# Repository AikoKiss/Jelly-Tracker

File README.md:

# Puchi Tracker
A smol-slime style tracker, with only the top-end parts, double-sided, NRF54L10 with ICM45686+QMC6309. Battery life is to be tested.

Thank you to Crylog for being an Absolute chad and unit of a PCB designer.
+ Mumo Tracker for the nice footprints and 3D files, making it easier to design the PCB.
+ Thank you, the slime community, for bullying all the bugs out of my design.
+ Special thanks to Meia for taking the time to help me squash all my stupid decisions and bugs.

## License

This project is source-available for personal and
educational use only.

Commercial use, manufacturing, resale, or distribution
For-profit is prohibited without written permission
from Limeneer Labs.

See the [LICENSE](LICENSE) file for full details.

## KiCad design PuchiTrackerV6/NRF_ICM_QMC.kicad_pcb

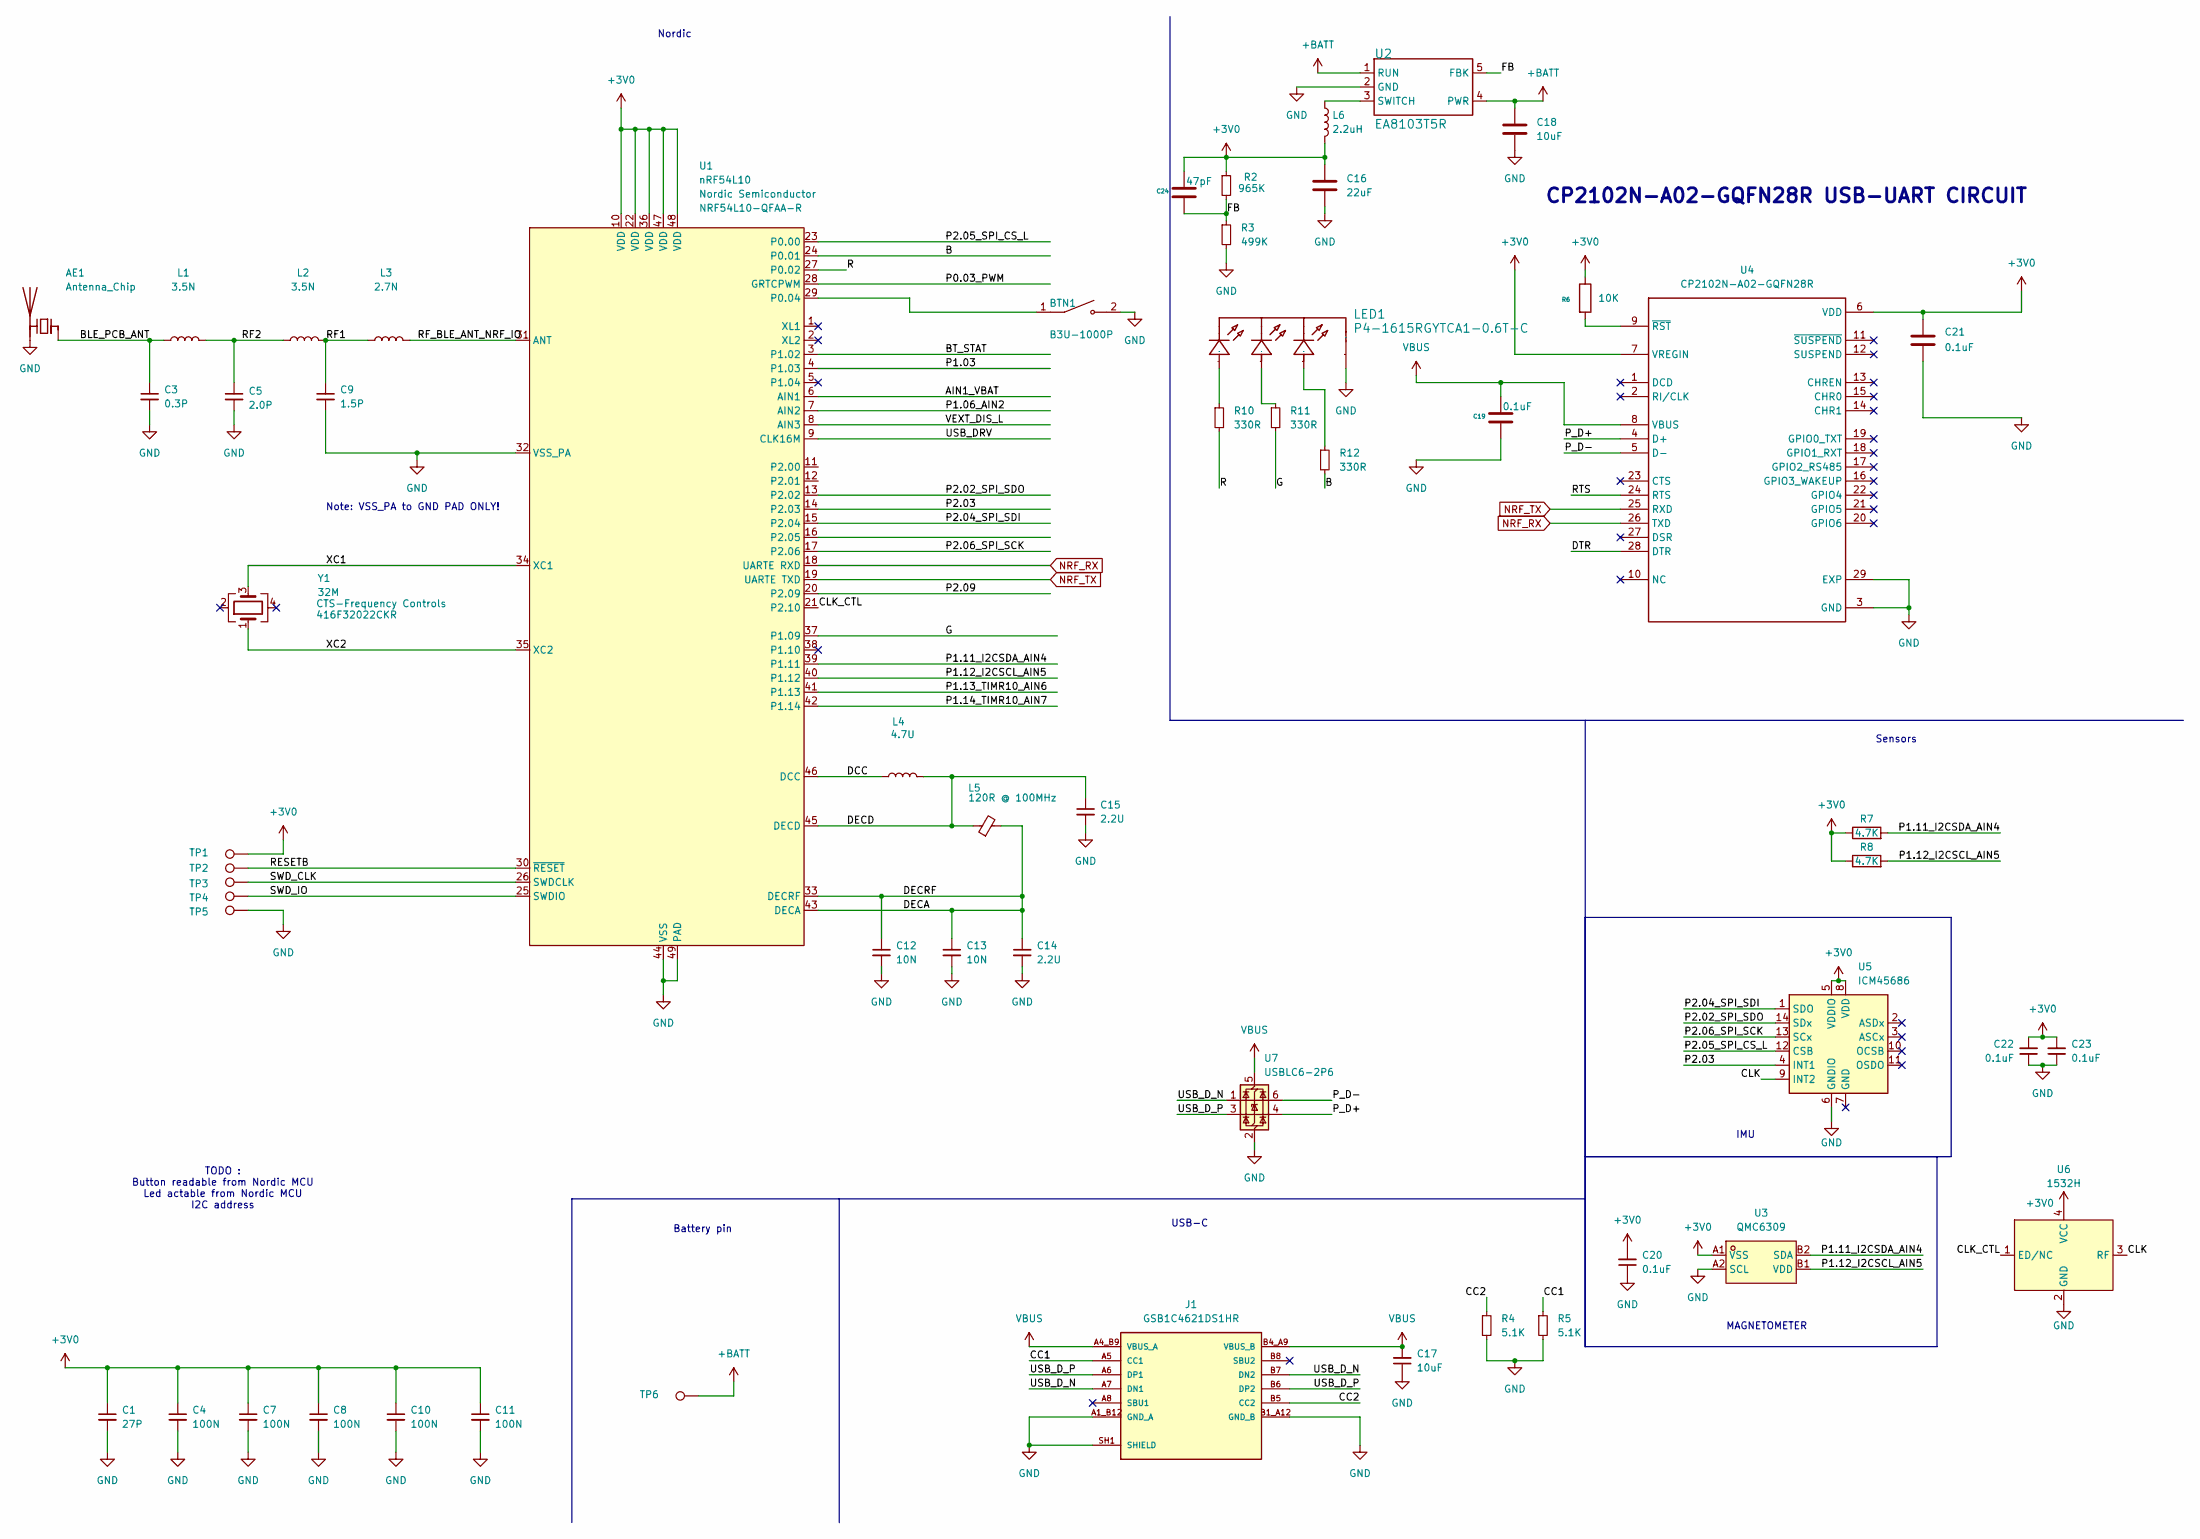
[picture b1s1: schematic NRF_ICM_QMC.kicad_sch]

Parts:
AE1: Antenna_Chip; MFG_PN 2450AT18A0100001E
BTN1: B3U-1000P; SW_SPST_B3U-1000P
C1: 27P; C_0402_1005Metric
C3: 0.3P; C_0402_1005Metric; MFG_PN GJM1555C1HR30WB01D
C4, C7, C8, C10, C11: 100N; C_0402_1005Metric
C5: 2.0P; C_0402_1005Metric; MFG_PN GJM0335C1E2R0WB01
C9: 1.5P; C_0402_1005Metric; MFG_PN GJM0335C1E1R5WB01
C12, C13: 10N; C_0402_1005Metric
C14, C15: 2.2U; C_0402_1005Metric
C16: 22uF; C_0402_1005Metric
C17, C18: 10uF; C_0402_1005Metric
C19, C20, C21, C22, C23: 0.1uF; C_0402_1005Metric
C24: 47pF; C_0402_1005Metric
J1: GSB1C4621DS1HR; AMPHENOL_GSB1C4621DS1HR; PARTREV AX1
L1, L2: 3.5N; L_0201_0603Metric; MFG_PN LQP03HQ3N5B02
L3: 2.7N; L_0201_0603Metric; MFG_PN LQP03HQ2N7B02
L4: 4.7U; L_0402_1005Metric; MFG_PN PLEA67BCA4R7M-1PT00
L5: 120R @ 100MHz; L_0201_0603Metric; MFG_PN BLM03AG121SN1D
L6: 2.2uH; L_1210_3225Metric
LED1: P4-1615RGYTCA1-0.6T-C; RGB; Manufacturer Part P4-1615RGYTCA1-0.6T-C; LCSC Part Name RGY三色
R2: 965K; R_0201_0603Metric
R3: 499K; R_0201_0603Metric
R4, R5: 5.1K; R_0201_0603Metric
R6: 10K; C_0402_1005Metric
R7, R8: 4.7K; R_0402_1005Metric
R10, R11, R12: 330R; R_0201_0603Metric
TP1, TP2, TP3, TP4, TP5, TP6: TestPoint; TestPoint_Pad_D1.0mm
U1: nRF54L10; QFN-48-1EP_6x6mm_P0.4mm_EP4.6x4.6mm; MFG_PN NRF54L10-QFAA-R
U2: EA8103T5R; Manufacturer Part EA8103T5R; LCSC Part Name 降压型 1.2A 2.6V~6V
U3: QMC6309; X1-WLB0808-4_L0.8-W0.8-P0.40-TL; MPN QMC6309; LCSC Part C5439871
U4: CP2102N-A02-GQFN28R; QFN-28-1EP_5x5mm_P0.5mm_EP3.1x3.1mm; PARTREV 1.5
U5: ICM45686; IMU (1)
U6: 1532H; CLK
U7: USBLC6-2P6; SOT-666
Y1: 32M; Oscillator_SMD_Abracon_ASCO-4Pin_1.6x1.2mm; MFG_PN 416F32022CKR

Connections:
+3V0: C1.1, C4.1, C7.1, C8.1, C10.1, C11.1, C16.1, C20.2, C21.1, C22.2, C23.2, C24.1, L6.2, R2.1, R6.1, R7.1, R8.1, TP1.1 (1_1), U1.10 (VDD), U1.22 (VDD), U1.36 (VDD), U1.47 (VDD), U1.48 (VDD), U3.A1 (VSS), U4.6 (VDD), U4.7 (VREGIN), U5.5 (VDDIO), U5.8 (VDD), U6.4 (VCC)
+BATT: C18.1, TP6.1 (1_1), U2.1 (RUN), U2.4 (PWR)
/AIN1_VBAT: U1.6 (AIN1)
/B: R12.2, U1.24 (P0.01)
/BLE_PCB_ANT: AE1.1 (FEED), C3.1, L1.1
/BT_STAT: U1.3 (P1.02)
/CC1: J1.A5 (CC1), R5.1
/CC2: J1.B5 (CC2), R4.1
/CLK: U5.9 (INT2), U6.3 (RF)
/CLK_CTL: U1.21 (P2.10), U6.1 (ED/NC)
/DCC: L4.1, U1.46 (DCC)
/DECA: C12.1, C13.1, C14.1, L5.2, U1.33 (DECRF), U1.43 (DECA)
/DECD: C15.1, L4.2, L5.1, U1.45 (DECD)
/DTR: U4.28 (DTR)
/FB: C24.2, R2.2, R3.1, U2.5 (FBK)
/G: R11.2, U1.37 (P1.09)
/P0.03_PWM: U1.28 (GRTCPWM)
/P1.03: U1.4 (P1.03)
/P1.06_AIN2: U1.7 (AIN2)
/P1.11_I2CSDA_AIN4: R7.2, U1.39 (P1.11), U3.B2 (SDA)
/P1.12_I2CSCL_AIN5: R8.2, U1.40 (P1.12), U3.B1 (VDD)
/P1.13_TIMR10_AIN6: U1.41 (P1.13)
/P1.14_TIMR10_AIN7: U1.42 (P1.14)
/P2.02_SPI_SDO: U1.13 (P2.02), U5.14 (SDx)
/P2.03: U1.14 (P2.03), U5.4 (INT1)
/P2.04_SPI_SDI: U1.15 (P2.04), U5.1 (SDO)
/P2.05_SPI_CS_L: U1.23 (P0.00), U5.12 (CSB)
/P2.06_SPI_SCK: U1.17 (P2.06), U5.13 (SCx)
/P2.09: U1.20 (P2.09)
/P_D+: U4.4 (D+), U7.4 (I/O2)
/P_D-: U4.5 (D-), U7.6 (I/O1)
/R: R10.2, U1.27 (P0.02)
/RESETB: TP2.1 (1_1), U1.30 (~RESET)
/RF1: C9.1, L2.2, L3.1
/RF2: C5.1, L1.2, L2.1
/RF_BLE_ANT_NRF_IO: L3.2, U1.31 (ANT)
/RTS: U4.24 (RTS)
/SWD_CLK: TP3.1 (1_1), U1.26 (SWDCLK)
/SWD_IO: TP4.1 (1_1), U1.25 (SWDIO)
/USB_DRV: U1.9 (CLK16M)
/USB_D_N: J1.A7 (DN1), J1.B7 (DN2), U7.1 (I/O1)
/USB_D_P: J1.A6 (DP1), J1.B6 (DP2), U7.3 (I/O2)
/VEXT_DIS_L: U1.8 (AIN3)
/XC1: U1.34 (XC1), Y1.3
/XC2: U1.35 (XC2), Y1.1
GND: AE1.2 (PCB_Trace), BTN1.2, C1.2, C3.2, C4.2, C5.2, C7.2, C8.2, C9.2, C10.2, C11.2, C12.2, C13.2, C14.2, C15.2, C16.2, C17.1, C18.2, C19.2, C20.1, C21.2, C22.1, C23.1, J1.A1_B12 (GND_A), J1.B1_A12 (GND_B), J1.SH1 (SHIELD), J1.SH2 (SHIELD), J1.SH3 (SHIELD), J1.SH4 (SHIELD), LED1.1 (V), R3.2, R4.2, R5.2, TP5.1 (1_1), U1.32 (VSS_PA), U1.44 (VSS), U1.49 (PAD), U2.2 (GND), U3.A2 (SCL), U4.3 (GND), U4.29 (EXP), U5.6 (GNDIO), U6.2 (GND), U7.2 (GND)
NRF_RX: U1.18 (UARTE RXD), U4.26 (TXD)
NRF_TX: U1.19 (UARTE TXD), U4.25 (RXD)
unnamed: LED1.4 (B), R12.1
unnamed: LED1.3 (G), R11.1
unnamed: LED1.2 (R), R10.1
unnamed: BTN1.1, U1.29 (P0.04)
unnamed: L6.1, U2.3 (SWITCH)
unnamed: R6.2, U4.9 (~RST)
VBUS: C17.2, C19.1, J1.A4_B9 (VBUS_A), J1.B4_A9 (VBUS_B), U4.8 (VBUS), U7.5 (VBUS)

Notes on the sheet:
Nordic
USB-C
MAGNETOMETER
TODO : Button readable from Nordic MCU Led actable from Nordic MCU I2C address
Note: VSS_PA to GND PAD ONLY!
IMU
Sensors
Battery pin
CP2102N-A02-GQFN28R USB-UART CIRCUIT

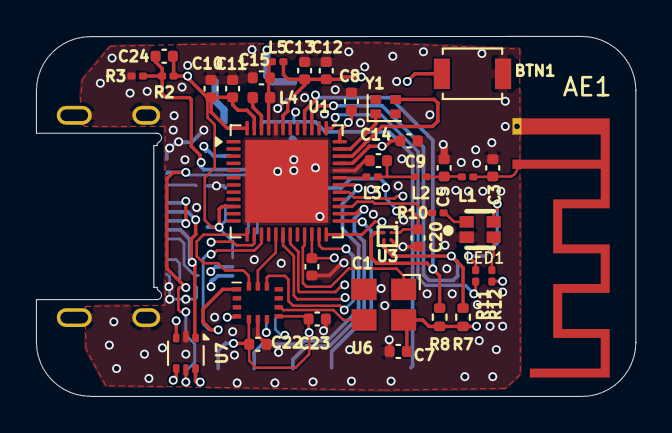
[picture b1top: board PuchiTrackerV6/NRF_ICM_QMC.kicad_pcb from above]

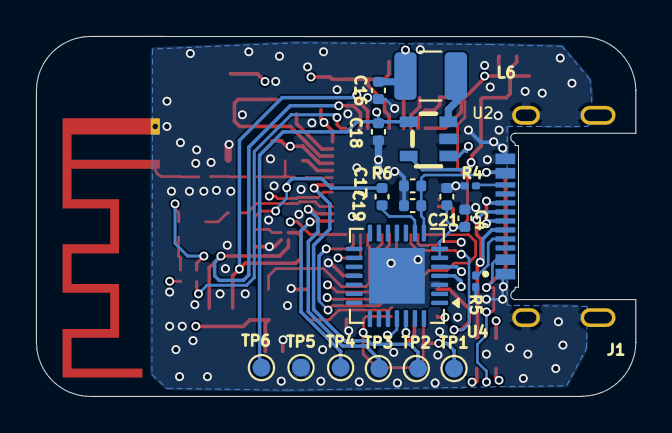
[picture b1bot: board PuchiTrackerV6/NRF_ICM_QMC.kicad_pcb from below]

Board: 4 copper layers, 33.3 x 20.0 mm, 56 parts (19 on the bottom side), 43 nets.

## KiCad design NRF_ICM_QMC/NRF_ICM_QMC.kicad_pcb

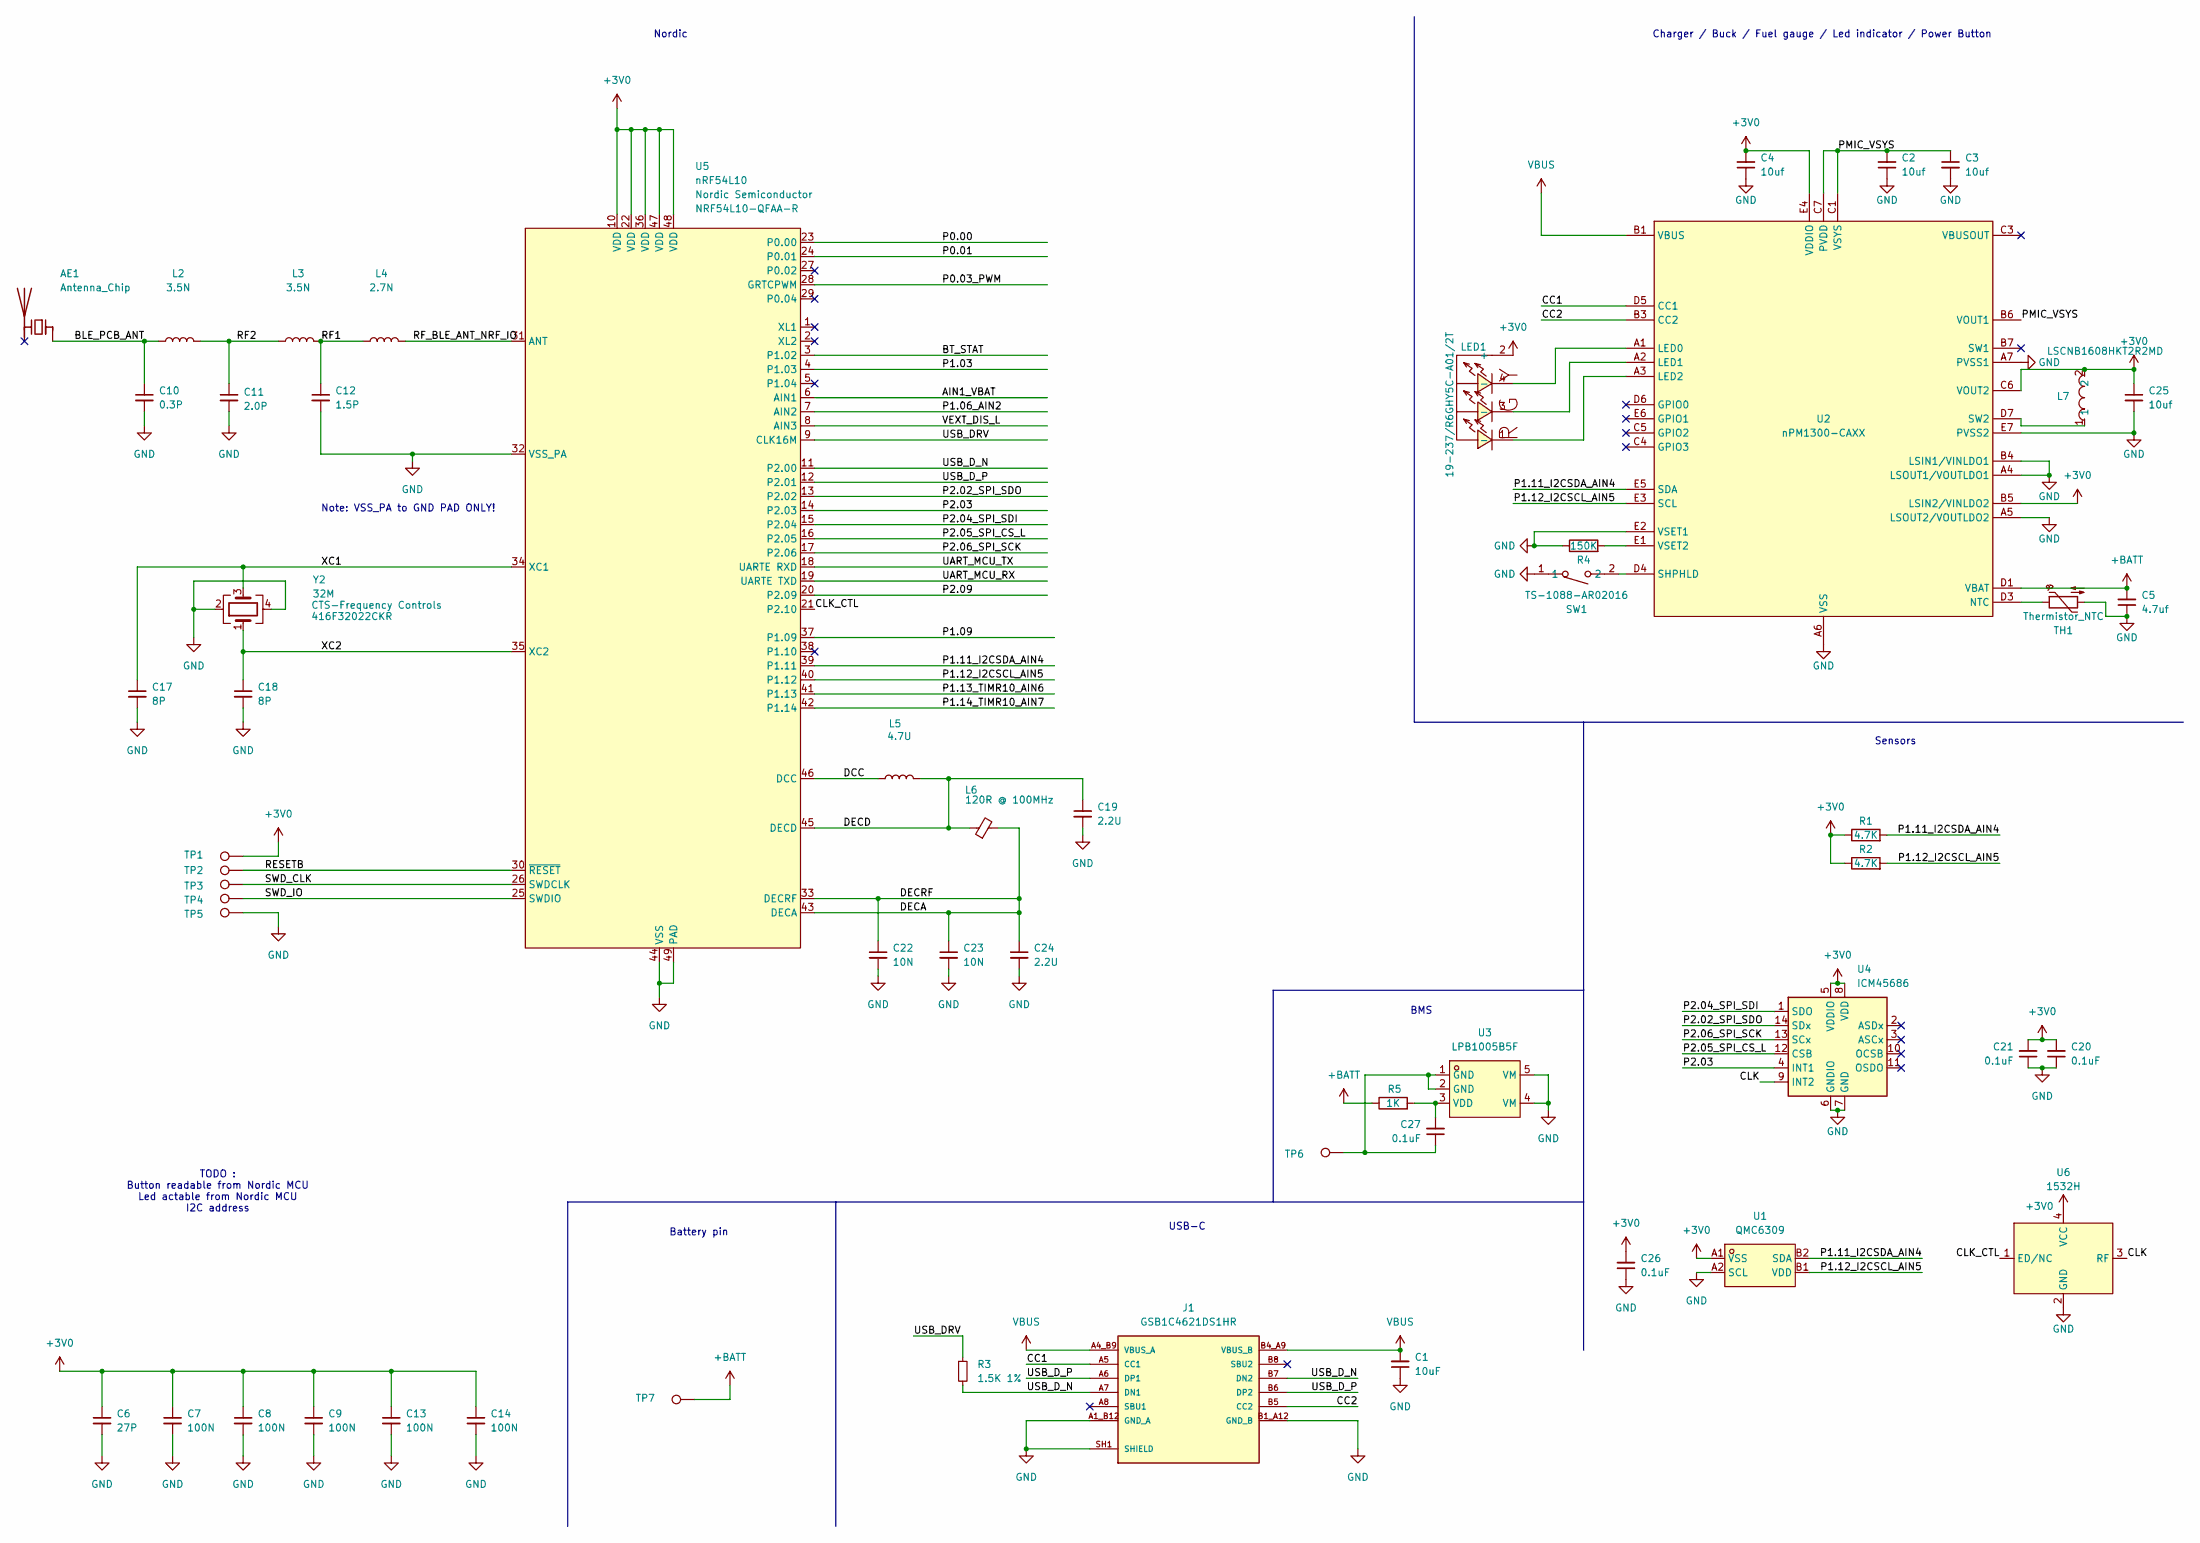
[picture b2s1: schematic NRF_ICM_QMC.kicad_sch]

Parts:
AE1: Antenna_Chip; Johanson_2450AT18x100; MFG_PN 2450AT18A0100001E
C1: 10uF; C_0805_2012Metric
C2, C3, C4, C25: 10uf; C_0805_2012Metric
C5: 4.7uf; C_0402_1005Metric
C6: 27P; C_0402_1005Metric
C7, C8, C9, C13, C14: 100N; C_0402_1005Metric
C10: 0.3P; C_0402_1005Metric; MFG_PN GJM1555C1HR30WB01D
C11: 2.0P; C_0402_1005Metric; MFG_PN GJM0335C1E2R0WB01
C12: 1.5P; C_0402_1005Metric; MFG_PN GJM0335C1E1R5WB01
C17, C18: 8P; C_0402_1005Metric
C19, C24: 2.2U; C_0402_1005Metric
C20, C21, C27: 0.1uF; C_0402_1005Metric
C22, C23: 10N; C_0402_1005Metric
C26: 0.1uF; C_0805_2012Metric
J1: GSB1C4621DS1HR; AMPHENOL_GSB1C4621DS1HR; PARTREV AX1
L2, L3: 3.5N; L_0201_0603Metric; MFG_PN LQP03HQ3N5B02
L4: 2.7N; L_0201_0603Metric; MFG_PN LQP03HQ2N7B02
L5: 4.7U; L_0402_1005Metric; MFG_PN PLEA67BCA4R7M-1PT00
L6: 120R @ 100MHz; L_0201_0603Metric; MFG_PN BLM03AG121SN1D
L7: LSCNB1608HKT2R2MD; L0603; MPN LSCNB1608HKT2R2MD; LCSC Part C6079477
LED1: 19-237/R6GHY5C-A01/2T; LED-ARRAY-SMD_4P-L1.6-W1.6-BL-CW; MPN 19-237/R6GHY5C-A01/2T; LCSC Part C2897364
R1, R2: 4.7K; R_0402_1005Metric
R3: 1.5K 1%; R_0201_0603Metric
R4: 150K; R_0402_1005Metric
R5: 1K
SW1: TS-1088-AR02016; SW-SMD_L3.9-W3.0-P4.45; MPN TS-1088-AR02016; LCSC Part C720477
TH1: Thermistor_NTC
TP1, TP2, TP3, TP4, TP5, TP6, TP7: TestPoint; TestPoint_Pad_D1.0mm
U1: QMC6309; X1-WLB0808-4_L0.8-W0.8-P0.40-TL; MPN QMC6309; LCSC Part C5439871
U2: nPM1300-CAXX; BGA-35_7x5_3.077x2.3775mm
U3: LPB1005B5F; SOT-23-5_L2.9-W1.6-P0.95-LS2.9-BL; MPN LPB1005B5F; LCSC Part C42460087
U4: ICM45686; Bosch_LGA-14_3x2.5mm_P0.5mm
U5: nRF54L10; QFN-48-1EP_6x6mm_P0.4mm_EP4.6x4.6mm; MFG_PN NRF54L10-QFAA-R
U6: 1532H; CLK
Y2: 32M; Oscillator_SMD_Abracon_ASCO-4Pin_1.6x1.2mm; MFG_PN 416F32022CKR

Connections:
+3V0: C4.2, C6.1, C7.1, C8.1, C9.1, C13.1, C14.1, C20.2, C21.2, C25.1, C26.2, L7.2, LED1.2 (+), R1.1, R2.1, TP1.1 (1_1), U1.A1 (VSS), U2.B5 (LSIN2/VINLDO2), U2.C6 (VOUT2), U2.E4 (VDDIO), U4.5 (VDDIO), U4.8 (VDD), U5.10 (VDD), U5.22 (VDD), U5.36 (VDD), U5.47 (VDD), U5.48 (VDD), U6.4 (VCC)
+BATT: C5.2, R5.1, TP7.1 (1_1), U2.D1 (VBAT), U2.D2 (VBAT)
/AIN1_VBAT: U5.6 (AIN1)
/BLE_PCB_ANT: AE1.1 (FEED_1), C10.1, L2.1
/BT_STAT: U5.3 (P1.02)
/CC1: J1.A5 (CC1), U2.D5 (CC1)
/CC2: J1.B5 (CC2), U2.B3 (CC2)
/CLK: U4.9 (INT2), U6.3 (RF)
/CLK_CTL: U5.21 (P2.10), U6.1 (ED/NC)
/DCC: L5.1, U5.46 (DCC)
/DECA: C22.1, C23.1, C24.1, L6.2, U5.33 (DECRF), U5.43 (DECA)
/DECD: C19.1, L5.2, L6.1, U5.45 (DECD)
/P0.00: U5.23 (P0.00)
/P0.01: U5.24 (P0.01)
/P0.03_PWM: U5.28 (GRTCPWM)
/P1.03: U5.4 (P1.03)
/P1.06_AIN2: U5.7 (AIN2)
/P1.09: U5.37 (P1.09)
/P1.11_I2CSDA_AIN4: R1.2, U1.B2 (SDA), U2.E5 (SDA), U5.39 (P1.11)
/P1.12_I2CSCL_AIN5: R2.2, U1.B1 (VDD), U2.E3 (SCL), U5.40 (P1.12)
/P1.13_TIMR10_AIN6: U5.41 (P1.13)
/P1.14_TIMR10_AIN7: U5.42 (P1.14)
/P2.02_SPI_SDO: U4.14 (SDx), U5.13 (P2.02)
/P2.03: U4.4 (INT1), U5.14 (P2.03)
/P2.04_SPI_SDI: U4.1 (SDO), U5.15 (P2.04)
/P2.05_SPI_CS_L: U4.12 (CSB), U5.16 (P2.05)
/P2.06_SPI_SCK: U4.13 (SCx), U5.17 (P2.06)
/P2.09: U5.20 (P2.09)
/PMIC_VSYS: C2.2, C3.1, U2.B6 (VOUT1), U2.C1 (VSYS), U2.C2 (VSYS), U2.C7 (PVDD)
/RESETB: TP2.1 (1_1), U5.30 (~RESET)
/RF1: C12.1, L3.2, L4.1
/RF2: C11.1, L2.2, L3.1
/RF_BLE_ANT_NRF_IO: L4.2, U5.31 (ANT)
/SWD_CLK: TP3.1 (1_1), U5.26 (SWDCLK)
/SWD_IO: TP4.1 (1_1), U5.25 (SWDIO)
/UART_MCU_RX: U5.19 (UARTE TXD)
/UART_MCU_TX: U5.18 (UARTE RXD)
/USB_DRV: R3.1, U5.9 (CLK16M)
/USB_D_N: J1.A7 (DN1), J1.B7 (DN2), R3.2, U5.11 (P2.00)
/USB_D_P: J1.A6 (DP1), J1.B6 (DP2), U5.12 (P2.01)
/VEXT_DIS_L: U5.8 (AIN3)
/XC1: C17.1, U5.34 (XC1), Y2.3
/XC2: C18.1, U5.35 (XC2), Y2.1
GND: C1.1, C2.1, C3.2, C4.1, C5.1, C6.2, C7.2, C8.2, C9.2, C10.2, C11.2, C12.2, C13.2, C14.2, C17.2, C18.2, C19.2, C20.1, C21.1, C22.2, C23.2, C24.2, C25.2, C26.1, J1.A1_B12 (GND_A), J1.B1_A12 (GND_B), J1.SH1 (SHIELD), J1.SH2 (SHIELD), J1.SH3 (SHIELD), J1.SH4 (SHIELD), R4.1, SW1.1, TH1.2, TP5.1 (1_1), U1.A2 (SCL), U2.A4 (LSOUT1/VOUTLDO1), U2.A5 (LSOUT2/VOUTLDO2), U2.A6 (VSS), U2.A7 (PVSS1), U2.B4 (LSIN1/VINLDO1), U2.E2 (VSET1), U2.E7 (PVSS2), U3.4 (VM), U3.5 (VM), U4.6 (GNDIO), U4.7 (GND), U5.32 (VSS_PA), U5.44 (VSS), U5.49 (PAD), U6.2 (GND), Y2.2, Y2.4; also elsewhere on the board
unnamed: C27.1, TP6.1 (1_1), U3.1 (GND), U3.2 (GND)
unnamed: LED1.4 (-), U2.A1 (LED0)
unnamed: LED1.3 (-), U2.A2 (LED1)
unnamed: LED1.1 (-), U2.A3 (LED2)
unnamed: TH1.1, U2.D3 (NTC)
unnamed: SW1.2, U2.D4 (SHPHLD)
unnamed: L7.1, U2.D7 (SW2)
unnamed: R4.2, U2.E1 (VSET2)
unnamed: C27.2, R5.2, U3.3 (VDD)
VBUS: C1.2, J1.A4_B9 (VBUS_A), J1.B4_A9 (VBUS_B), U2.B1 (VBUS), U2.B2 (VBUS)

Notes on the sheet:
Nordic
USB-C
TODO : Button readable from Nordic MCU Led actable from Nordic MCU I2C address
Note: VSS_PA to GND PAD ONLY!
BMS
Sensors
Battery pin
Charger / Buck / Fuel gauge / Led indicator / Power Button

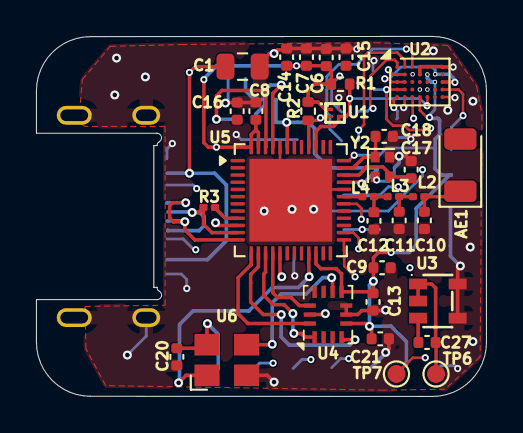
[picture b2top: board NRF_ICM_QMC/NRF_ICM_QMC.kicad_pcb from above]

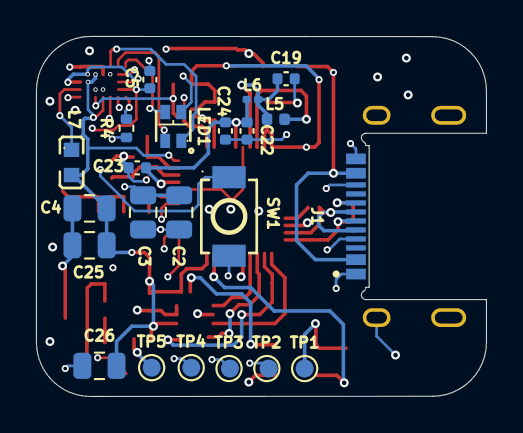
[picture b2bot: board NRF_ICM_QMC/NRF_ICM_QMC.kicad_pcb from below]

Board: 4 copper layers, 25.0 x 20.0 mm, 55 parts (22 on the bottom side), 39 nets.

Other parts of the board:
C15, C16: 9P; C_0402_1005Metric

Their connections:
GND: C15.2, C16.2; also elsewhere on the board

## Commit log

2026-05-19 Add Creative Commons Attribution 4.0 License
    Added the Creative Commons Attribution 4.0 International Public License to the project.
2026-05-19 First Upload
2026-05-19 Revise LICENSE to proprietary terms and conditions
    Updated the license terms to reflect proprietary ownership and restrictions on use.
2026-05-19 LICENSE to include personal use terms
    Updated the LICENSE file to include the Limeneer Labs Personal Use License (LPL) terms and conditions.
2026-05-19 Update README with license details and badge
    Added license information and badge to README.
2026-05-19 Update README with acknowledgments
    Added acknowledgments for PCB design contributions.
2026-05-24 Update README with acknowledgments and community thanks
    Added acknowledgments for contributors and community support.
2026-06-04 V2
    Fixed EVERYTHING, i Think
2026-06-06 V3
    Updated, with fixes
2026-06-06 Delete PuchiTrackerV2 directory
    Old Ver delete
2026-06-07 Delete PuchiTrackerV3 directory
    Update to V4
2026-06-07 V4 Puchi Tracker
    Fixed Atenna, DC/DC improvement, moved cs pin to p0.00
2026-06-08 Update README for clarity and grammar improvements
    Corrected grammar and improved clarity in the README and additional thanks to Meia.
2026-06-08 PuchiV5
    Fixed More stuff
2026-06-14 PuchiTrackerV6
    V6 Update, Changed Layer stack
2026-06-17 PuchiTrackerV6
    Fixed and ready to go

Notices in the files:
README.md:
License: Proprietary
